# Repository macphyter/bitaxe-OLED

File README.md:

# bitaxe-OLED
bitaxe-OLED is a carrier board for a specific 1.9 inch 170x320 OLED
which is intended to connect to a bitaxe device via the BAP (Bitaxe Accessory Port)

Here is the OLED display

The display attaches to the front of the carrier board using double sided foam tape, and 
the connector wraps around through the notch and attaches to the 30-pin connector on the back.

This OLED display uses a ST7789 controller and can operate in parallel mode or SPI mode
through its 30-pin connector.  The carrier board uses an STM32 MCU to drive the OLED 
and the hardware is designed to support either parallel or SPI mode, depending on the 
needs of the firmware developer.

The pins used to support each interface are described in this table

The MCU firmware is flashed using the built-in STM32 serial bootloader which is activated 
by holding down the "boot" button while powering on the board.  A standard FTDI cable 
pinout was used to make firmware flashing easy but this pinout is not identical to the 
Bitaxe BAP, so a custom cable solution may be necessary to connect this to a bitaxe.

The MCU firmware will display various GUI pages, and the data for these pages will be 
supplied by the bitaxe through the UART.

The MCU is an STM32G0B1KEU6 which has 512KB of flash memory and 144K of RAM, and runs at 
64 MHz from the internal oscillator.

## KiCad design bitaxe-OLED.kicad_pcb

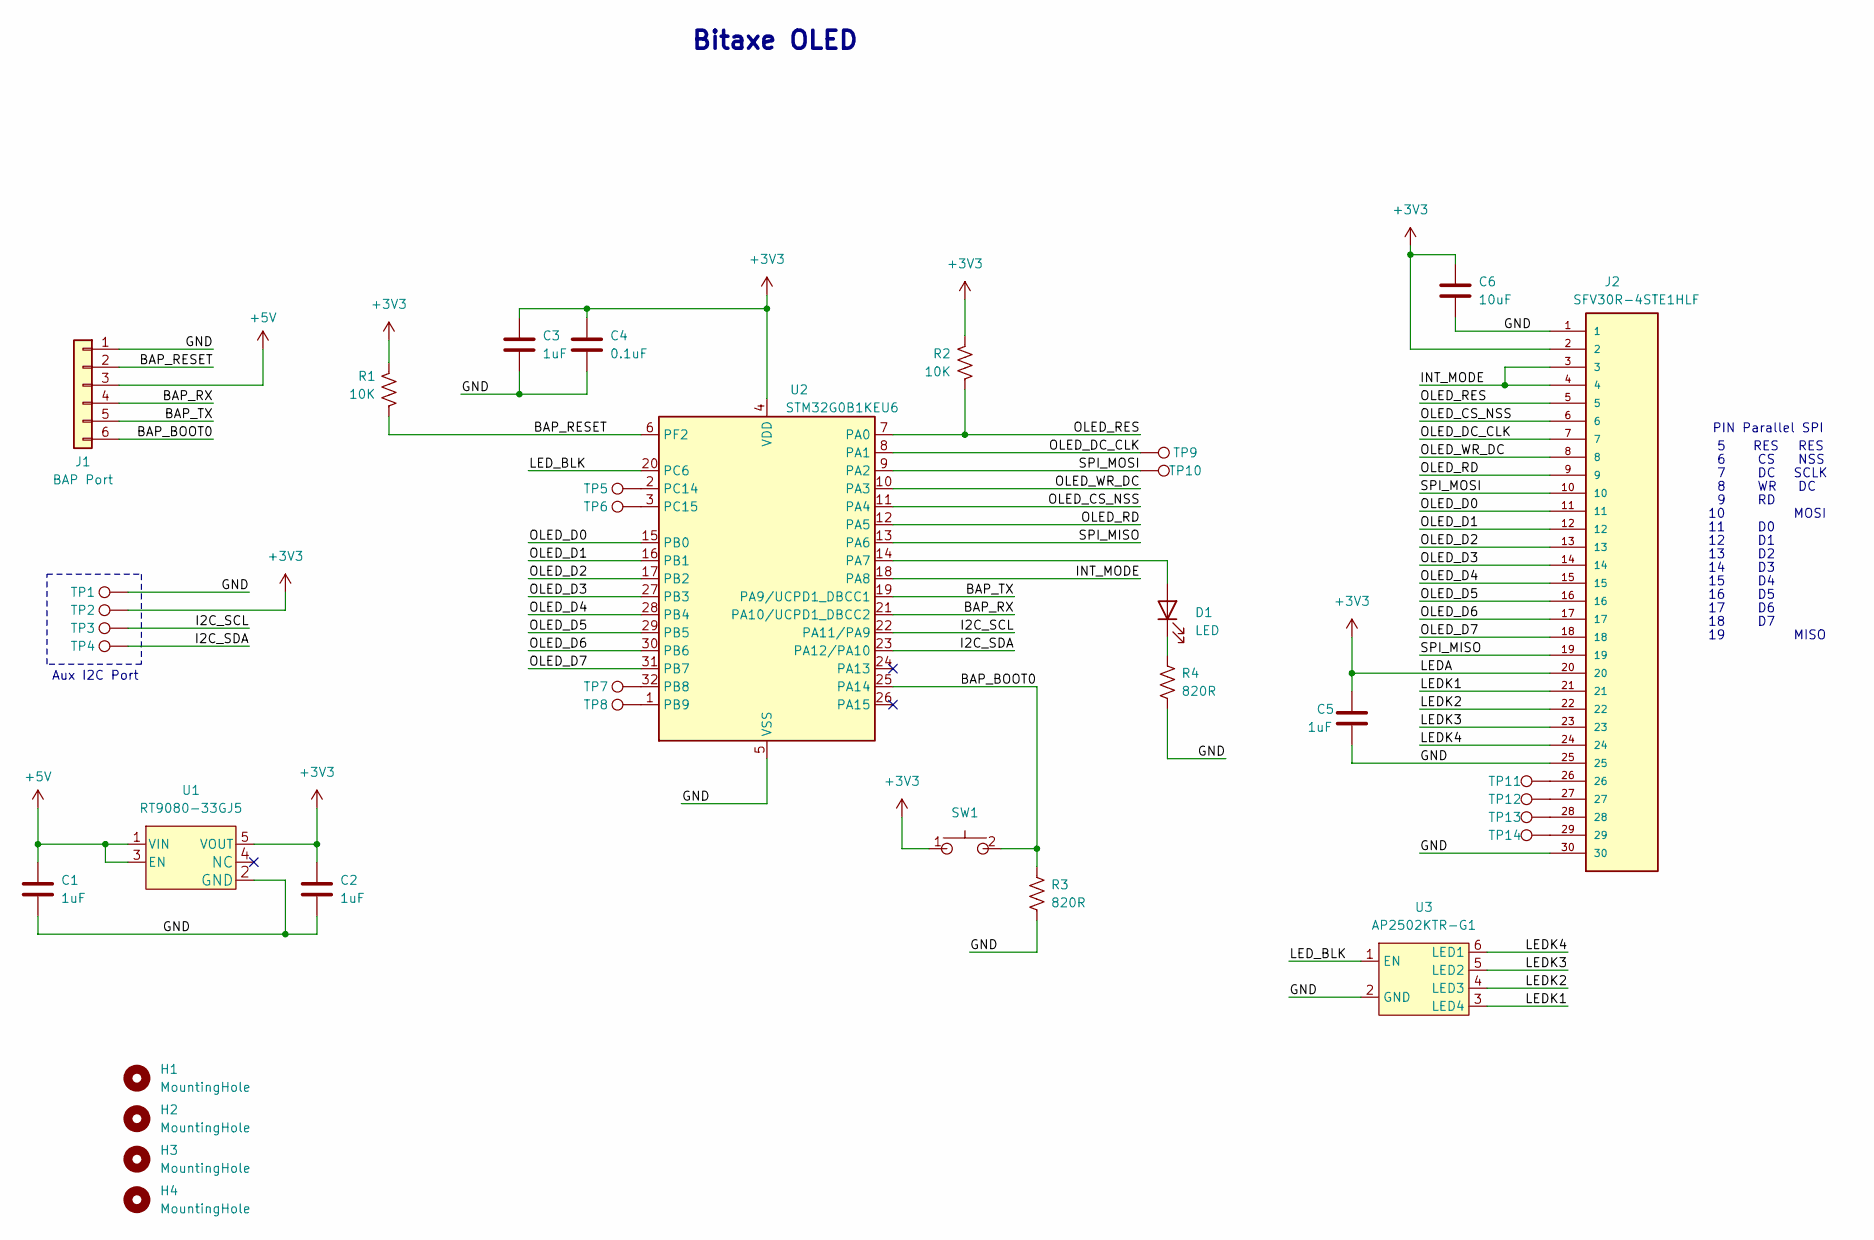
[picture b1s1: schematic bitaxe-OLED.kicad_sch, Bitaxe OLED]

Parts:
C1, C2, C3, C5: 1uF; C_0402_1005Metric
C4: 0.1uF; C_0402_1005Metric
C6: 10uF; C_0603_1608Metric
D1: LED; LED_0603_1608Metric
H1, H2, H3, H4: MountingHole; MountingHole_3.2mm_M3_Pad_Via
J1: BAP Port; PinHeader_1x06_P2.54mm_Vertical
J2: SFV30R-4STE1HLF; AMPHENOL_SFV30R-4STE1HLF; PARTNO SFV30R-4STE1HLF; JLCPCB KH-FG0.5-H2.0-30PIN
R1, R2: 10K; R_0402_1005Metric
R3, R4: 820R; R_0402_1005Metric
SW1: SWITCH-SPST; switch-TL3301; PARTNO EVQ-9P701P
TP1, TP2, TP3, TP4: TestPoint; TestPoint_Pad_D1.5mm
TP5, TP6, TP7, TP8, TP9, TP10, TP11, TP12, TP13, TP14: TestPoint; TestPoint_Pad_D1.0mm
U1: RT9080-33GJ5; PARTNO RT9080-33GJ5
U2: STM32G0B1KEU6; QFN-32-1EP_5x5mm_P0.5mm_EP3.45x3.45mm
U3: AP2502KTR-G1; SOT-23-6; PARTNO CLX6E-FKC-CH1M1D1BB7C3D3

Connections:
+3V3: C2.1, C3.1, C4.1, C5.1, C6.2, J2.2, J2.20, R1.1, R2.2, SW1.1, TP2.1, U1.5 (VOUT), U2.4 (VDD)
+5V: C1.1, J1.3, U1.1 (VIN), U1.3 (EN)
/BAP_BOOT0: J1.6, R3.2, SW1.2, U2.25 (PA14)
/BAP_RESET: J1.2, R1.2, U2.6 (PF2)
/BAP_RX: J1.4, U2.21 (PA10/UCPD1_DBCC2)
/BAP_TX: J1.5, U2.19 (PA9/UCPD1_DBCC1)
/GND: C1.2, C2.2, C3.2, C4.2, C5.2, C6.1, J1.1, J2.1, J2.25, J2.30, R3.1, R4.1, TP1.1, U1.2 (GND), U2.5 (VSS), U2.33 (VSS), U3.2 (GND)
/I2C_SCL: TP3.1, U2.22 (PA11/PA9)
/I2C_SDA: TP4.1, U2.23 (PA12/PA10)
/INT_MODE: J2.3, J2.4, U2.18 (PA8)
/LEDK1: J2.21, U3.3 (LED4)
/LEDK2: J2.22, U3.4 (LED3)
/LEDK3: J2.23, U3.5 (LED2)
/LEDK4: J2.24, U3.6 (LED1)
/LED_BLK: U2.20 (PC6), U3.1 (EN)
/OLED_CS_NSS: J2.6, U2.11 (PA4)
/OLED_D0: J2.11, U2.15 (PB0)
/OLED_D1: J2.12, U2.16 (PB1)
/OLED_D2: J2.13, U2.17 (PB2)
/OLED_D3: J2.14, U2.27 (PB3)
/OLED_D4: J2.15, U2.28 (PB4)
/OLED_D5: J2.16, U2.29 (PB5)
/OLED_D6: J2.17, U2.30 (PB6)
/OLED_D7: J2.18, U2.31 (PB7)
/OLED_DC_CLK: J2.7, TP9.1, U2.8 (PA1)
/OLED_RD: J2.9, U2.12 (PA5)
/OLED_RES: J2.5, R2.1, U2.7 (PA0)
/OLED_WR_DC: J2.8, U2.10 (PA3)
/SPI_MISO: J2.19, U2.13 (PA6)
/SPI_MOSI: J2.10, TP10.1, U2.9 (PA2)
unnamed: D1.2 (A), U2.14 (PA7)
unnamed: D1.1 (K), R4.2
unnamed: J2.26, TP11.1
unnamed: J2.27, TP12.1
unnamed: J2.28, TP13.1
unnamed: J2.29, TP14.1
unnamed: TP7.1, U2.32 (PB8)
unnamed: TP8.1, U2.1 (PB9)
unnamed: TP5.1, U2.2 (PC14)
unnamed: TP6.1, U2.3 (PC15)

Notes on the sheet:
SCLK
MOSI
RES
MISO
Aux I2C Port
PIN Parallel SPI
NSS
Bitaxe OLED

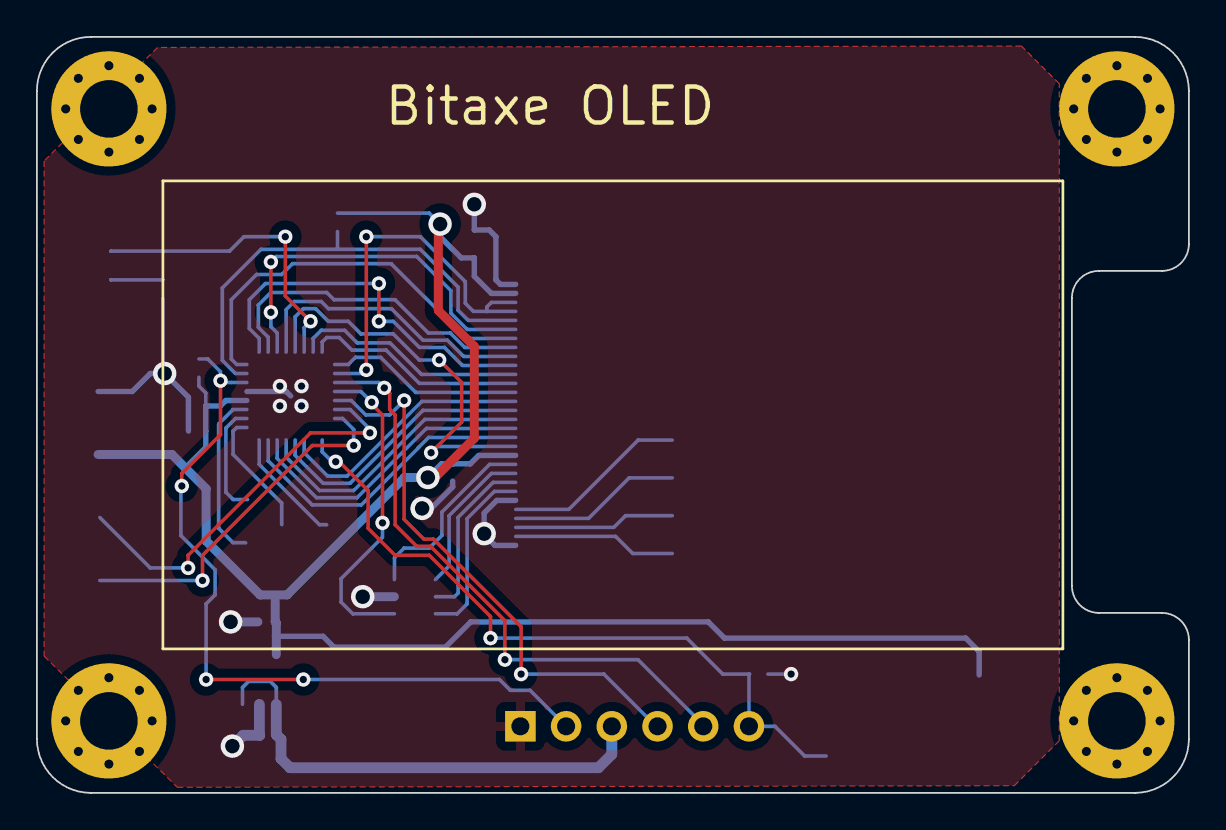
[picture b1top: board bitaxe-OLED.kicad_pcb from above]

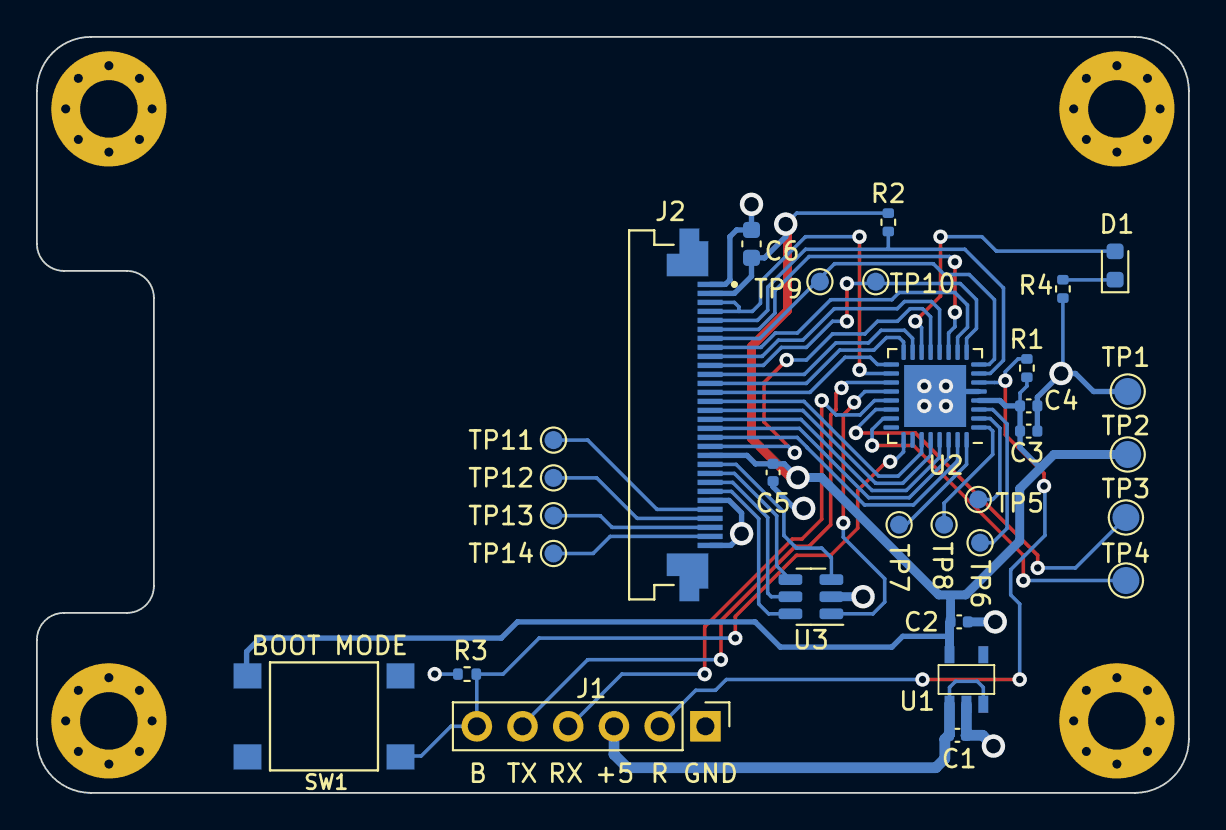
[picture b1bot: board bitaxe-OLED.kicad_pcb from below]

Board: 2 copper layers, 64.0 x 42.0 mm, 35 parts (31 on the bottom side), 40 nets.

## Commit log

2024-03-17 start work on README
2024-03-17 add interface modes table
2024-03-17 add LICENSE
